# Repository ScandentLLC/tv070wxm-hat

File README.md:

# TV070WXM-HAT

A Raspberry Pi 5 HAT form-factor adapter that connects the **BOE TV070WXM-TV1-3GP1** MIPI-DSI LCD touch panel (the same display used in the LCD Steam Deck) to a Raspberry Pi 5.

<table>
  <tr>
    <td align="center"></td>
    <td align="center"></td>
  </tr>
  <tr>
    <td align="center"><b>Front</b></td>
    <td align="center"><b>Back</b></td>
  </tr>
</table>

## Description

The TV070WXM-HAT breaks out a MIPI-DSI + touch interface so you can drive the **BOE TV070WXM-TV1-3GP1** panel (the original Steam Deck LCD) directly from a Raspberry Pi 5. Two flat-flex cables carry DSI/touch between the Pi's DISP connector, the HAT, and the panel, and a 3D-printed bracket holds the whole stack together behind the display.

## What's in this repo

- **KiCad project** — schematic (with full BOM), board layout, and Gerbers, ready to send to a fab.
- **3D-printable bracket** — a simple STEP that sandwiches the Pi 5, HAT, and panel into one rigid assembly.
- **Linux Kernel patch** — a patch containing the driver and DTS files needed to make the display work on Linux.

## Parts needed for assembly

> [!WARNING]
> **This HAT is only expected to work with the official Raspberry Pi 5 27 W (5.1 V / 5 A) USB-C power supply.**
> Other power supplies will cause instability and brownouts unless they support 5 A current via USB-PD negotiation This is incredibly rare.

| Qty | Item | Digi-Key P/N | Notes |
|:---:|------|--------------|-------|
| 1 | BOE TV070WXM-TV1-3GP1 panel | — | The Steam Deck LCD panel |
| 1 | Raspberry Pi 5 (with SD card) | — | |
| 1 | Raspberry Pi 5 official 27 W PSU | — | **Required** — see warning above |
| 1 | TV070WXM-HAT | — | This project — fab it from the included Gerbers |
| 1 | FFC, Pi 5 ↔ HAT | `2073-05-22-D-0030-A-4-06-4-T-ND` | 22-pin, 0.5 mm, 30 mm, opposite-side contacts (GCT type D) |
| 1 | FFC, HAT ↔ display panel | `WM9283-ND` | Molex 0150150239 — 39-pin, 0.3 mm, 2" |
| 1 | 3D-printed bracket | — | STEP in this repo |
| 4 | 8mm M2.5X0.45 flat head screws | McMaster P/N 92010A018 | Source : McMaster Carr| 
| 4 | 2.54 mm round nylon spacers | `492-1768-ND` | Between bracket and Pi 5 |
| 4 | 11 mm M2.5×0.45 F/F standoffs | `R25-1001102-ND` | Between Pi 5 and HAT **(See note about accommodating heatsink/cooler)**|
| 4 | 8 mm M2.5×0.45 M/F standoffs | `AE10794-ND` | Above the HAT — the feet the assembly stands on |

## Assembly

> [!NOTE]
> This HAT is also compatible with the CM4 IO board, but it would require a much longer FFC between the DISP1 of the CM4 IO board and the J2 of the HAT to work. However, the hardware documentation focuses exclusively on the Raspberry Pi 5. The software documentation below includes instructions for the CM4.

### Step 1 — Mount the Pi 5 to the bracket

Using the screws, the white plastic spacers, and the female-to-female standoffs, secure the Raspberry Pi 5 to the bracket. The stack order at each corner is: **screw → spacer → Pi 5 → standoff**.
<table>
  <tr>
    <td align="center"></td>
    <td align="center"></td>
  </tr>
  </table>

### Step 2 — Connect and mount the HAT

> [!NOTE]
> To fit a Raspberry Pi 5 heatsink/active cooler between the Pi 5 and the HAT, you'll need a **taller GPIO header extender** and **longer standoffs** to clear the cooler's height. For the GPIO extender, consider Digikey P/N 1568-16763-ND, and for the longer standoffs (alternative to the 11mm standoffs), consider 25mm (Digikey P/N AE10862-ND) or 30mm (Digikey P/N 732-10626-ND)

Plug the small FFC ZIF cable into the **CAM/DISP1 connector** on the Pi 5, and plug the other end into the HAT. Seat the ZIF cable **before** mounting the HAT onto the 40-pin header — it's much easier that way. Then mount the HAT onto the Pi 5 and screw the male-female standoffs into the corners of the HAT. These are the legs the assembly stands on.
<table>
  <tr>
    <td align="center"></td>
    <td align="center"></td>
  </tr>
  </table>

### Step 3 — Connect the panel

Place the bracket on top of the display, then plug in the second FFC ZIF connector between the HAT and the display panel. Turn the assembly around and the hardware is ready.

## Driver / software

The display will not light up on hardware alone — it needs a Linux kernel panel driver and matching device-tree overlays.

This repository includes the interim kernel patch:

**[`linux-rpi-6.12.y-panel-boe-tv070wxm.patch`](./linux-rpi-6.12.y-panel-boe-tv070wxm.patch)**

The long-term plan is to submit the driver to Linux mainline. Until that happens, apply the patch against the raspberrypi/linux tree's `rpi-6.12.y` branch.

### Building the kernel

The patch was developed against the `rpi-6.12.y` branch (commit `5f23da14d91d4ba66604ec75453564e4e2afc57e`) and applies cleanly to the tip of that branch as of commit `f5a99b95354d38db209003a7d00560e5091ba94a`.

1. Obtain the Raspberry Pi kernel sources for the `rpi-6.12.y` branch.
2. Apply the patch:

   ```bash
   git apply linux-rpi-6.12.y-panel-boe-tv070wxm.patch
   ```

   (or `patch -p1 < linux-rpi-6.12.y-panel-boe-tv070wxm.patch`)

3. Enable the driver in your kernel `.config`:

   ```
   CONFIG_DRM_PANEL_BOE_TV070WXM=m
   ```

4. Build and install the kernel the same way you normally build a custom Raspberry Pi kernel. See the official [Raspberry Pi documentation](https://www.raspberrypi.com/documentation/computers/linux_kernel.html) if necessary.

Once the driver is accepted upstream you can simply use a Raspberry Pi or mainline kernel that already contains it.

> [!TIP]
> If using a custom kernel before the driver is accepted upstream, use an alternative kernel name such as `kernel_2712-custom.img` and edit config.txt to specify `kernel=kernel_2712-custom.img`. Without this, system updates will replace the kernel, causing black screens on reboot from the lack of a driver. Also, you will likely want to regenerate a corresponding initramfs using update-initramfs.

### Device-tree overlays (`config.txt`)

> [!NOTE]
> Unlike official HAT/HAT+ accessories, this does not include an ID EEPROM for auto-loaded overlays.

#### Raspberry Pi 5 (and CM5)

Add the following lines to `/boot/firmware/config.txt`:

```
display_auto_detect=0
dtoverlay=vc4-kms-v3d-pi5
dtoverlay=boe-tv070wxm-pi5
```

The Raspberry Pi 5 instructions are expected to work on the CM5 as well, but it is untested.

#### Compute Module 4

Add the following lines to `/boot/firmware/config.txt`:

```
display_auto_detect=0
dtoverlay=vc4-kms-v3d
dtoverlay=boe-tv070wxm
```

### X11 configuration (rotation & touch)

> [!NOTE]
> Only X11 is tested. Current Raspberry Pi OS defaults to Wayland. Switch to X11 in raspi-config (Advanced Options → Wayland) before using the config below.

On the Steam Deck, screen rotation is handled by `drm_panel_orientation_quirks.c` using DMI data that does not exist on the Raspberry Pi, and touch-input rotation is performed in userspace. Consequently an X11 configuration file is required (unless you prefer the display's native portrait orientation). The Linux kernel obtains a landscape orientation from the DTS for the kernel console, but nothing else uses that.

#### Raspberry Pi 5 (and CM5)

Install the following file:

```bash
cat << 'END' | sudo tee /usr/share/X11/xorg.conf.d/95-touch-rotate.conf
Section "Monitor"
    Identifier "DSI-2"
    Option "Rotate" "left"
EndSection

Section "InputClass"
    Identifier "Steam Deck Touchscreen"
    MatchProduct "hid-over-i2c 2808:1015"
    MatchIsTouchscreen "on"
    Option "TransformationMatrix" "0 -1 1 1 0 0 0 0 1"
EndSection
END
```

This is expected to work on the CM5 as well, but it is untested.

After a reboot the panel should display text in a landscape orientation with a working touchscreen.

#### Compute Module 4

Install the following file:

```bash
cat << 'END' | sudo tee /usr/share/X11/xorg.conf.d/95-touch-rotate.conf
Section "Monitor"
    Identifier "DSI-1"
    Option "Rotate" "left"
EndSection

Section "InputClass"
    Identifier "Steam Deck Touchscreen"
    MatchProduct "hid-over-i2c 2808:1015"
    MatchIsTouchscreen "on"
    Option "TransformationMatrix" "0 -1 1 1 0 0 0 0 1"
EndSection
END
```

After a reboot the panel should display text in a landscape orientation with a working touchscreen.

## Purpose

We originally developed this for our own internal use at Scandent LLC. The first iteration was an adapter board for the CM4 IO that we created as a development artifact that allowed us to bring up the Steam Deck LCD on the CM4 without investing into a full custom CM4 carrier board spin before we knew whether it would work.

We love open source and wish to share what we can with others for their reuse. Thus, after we confirmed that this worked, we redesigned our adapter board into a HAT form factor. It is our hope that others will find what we have done useful and incorporate it into their own projects. This includes the creation of commercial versions. For that reason, we have selected the CC0-1.0 license for our hardware, to ensure that there are no barriers to third party use.

For those who do incorporate this into their own CM4/CM5 carrier boards, note that very careful attention must be given to the MIPI DSI lane lengths and signal integrity.

## License

Unless otherwise specified, files in this repository are licensed under the CC0-1.0 license. See [`LICENSE`](LICENSE).

The linux kernel patch is the primary (and at the time of writing, the only) exception. It is licensed under the GPLv2.

## Credits
- Hardware engineering / documentation — Akshay Athalye
- Software engineering / documentation — Richard Yao
- HAT Evaluation / Comments — Jeff Geerling

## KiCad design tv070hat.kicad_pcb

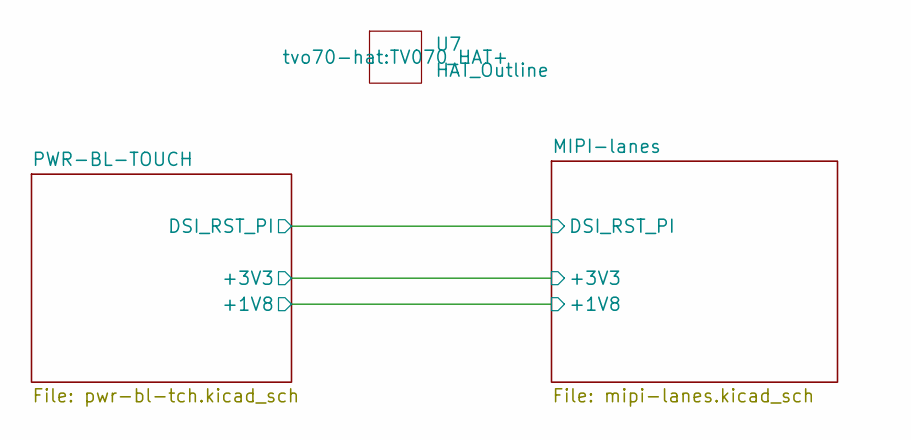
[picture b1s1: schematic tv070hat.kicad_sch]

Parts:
U7: HAT_Outline; TV070_HAT+

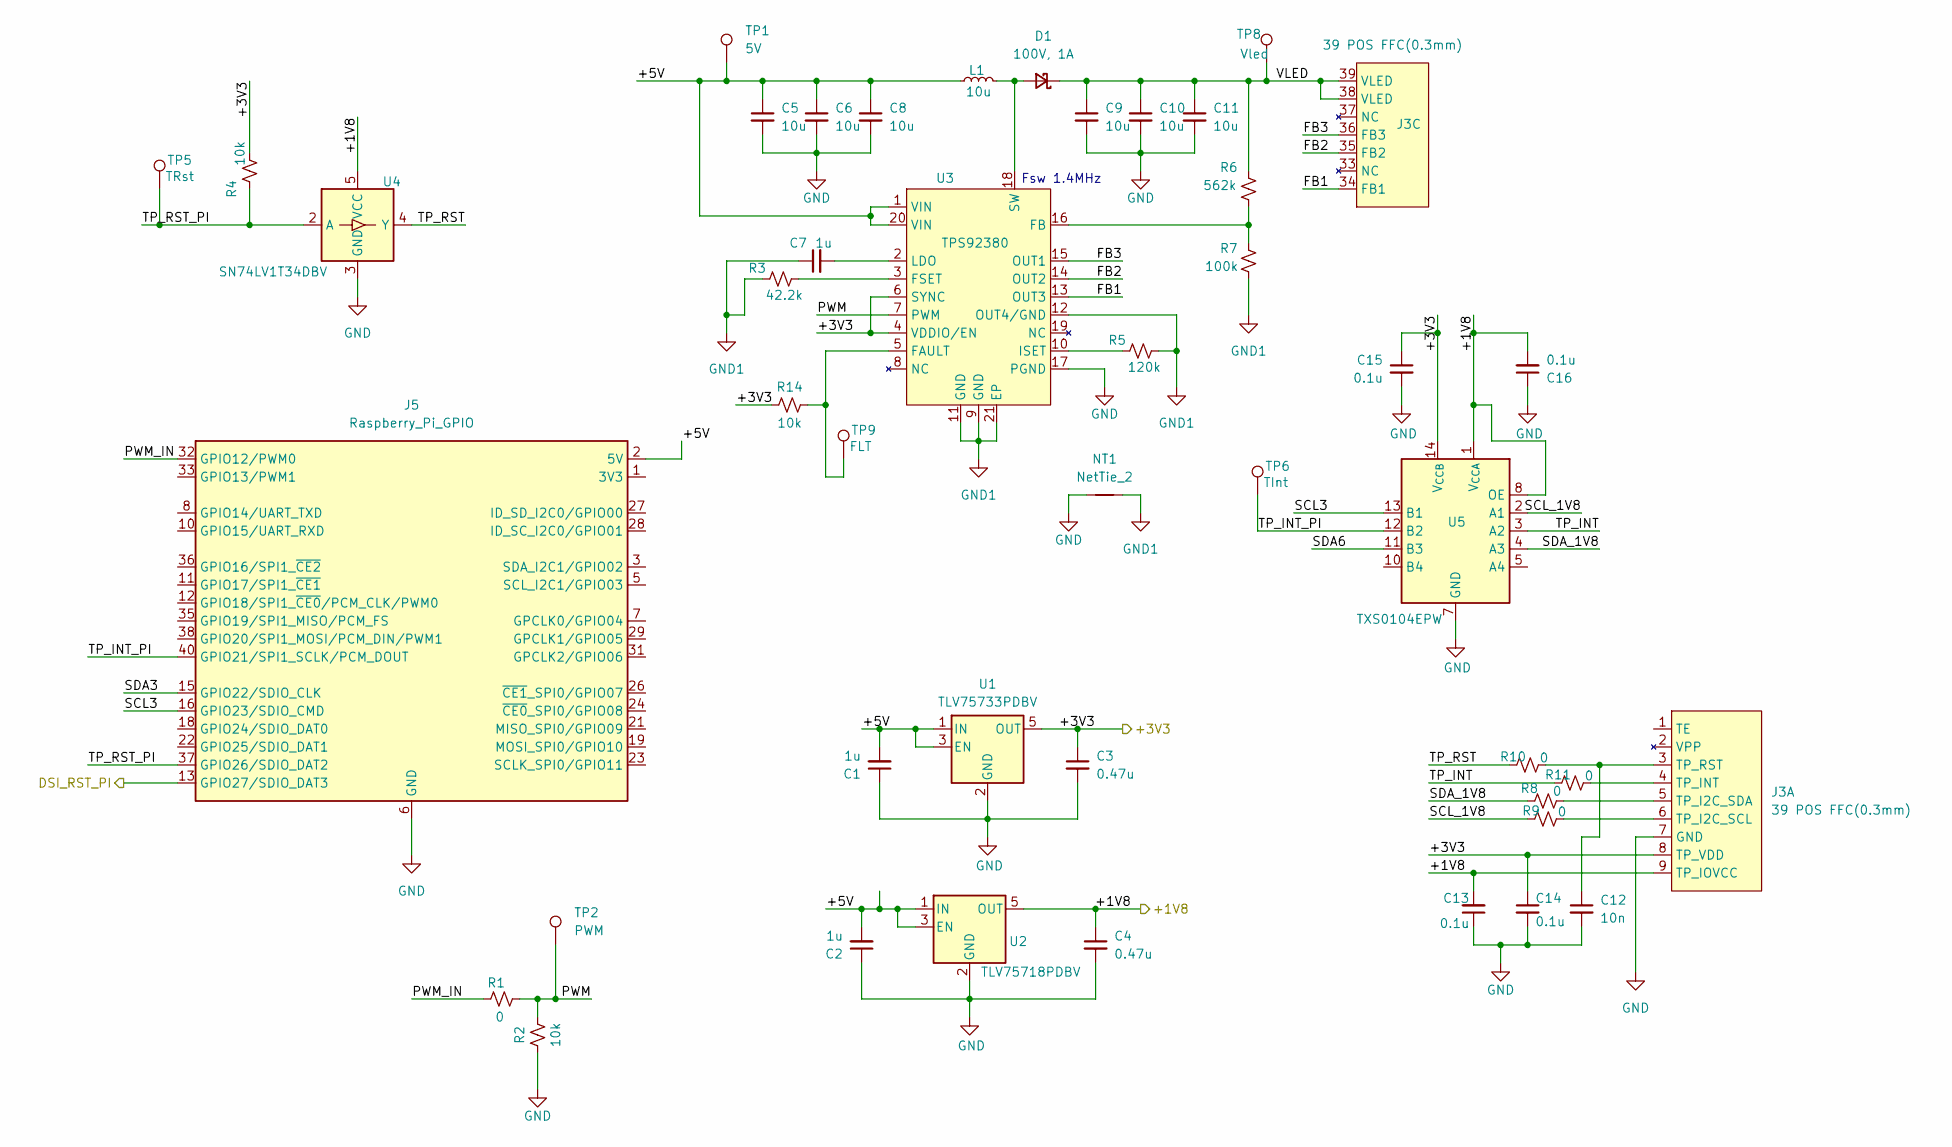
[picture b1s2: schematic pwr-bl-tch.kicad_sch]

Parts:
C1, C2, C7: 1u; C_0603_1608Metric; Mfg. Part No. CL10B105KA8NNNC; Digikey Part No. 1276-1184-1-ND
C3, C4: 0.47u; C_0603_1608Metric; Mfg. Part No. CL10B474KA8NFNC; Digikey Part No. 1276-2082-1-ND
C5, C6, C8: 10u; C_0805_2012Metric; Mfg. Part No. CL21B106KAYQNNE; Digikey Part No. 1276-CL21B106KAYQNNECT-ND
C9, C10, C11: 10u; C_1206_3216Metric; Mfg. Part No. CL31B106KBHNNNE; Digikey Part No. 1276-6767-1-ND
C12: 10n; C_0402_1005Metric; Mfg. Part No. GRM155R71C103KA01D; Digikey Part No. 490-1313-1-ND
C13, C14: 0.1u; C_0402_1005Metric; Mfg. Part No. CL05B104KP5NNNC; Digikey Part No. 1276-1002-1-ND
C15, C16: 0.1u; C_0603_1608Metric; Mfg. Part No. CL10B104KO8NNNC; Digikey Part No. 1276-1005-1-ND
D1: 100V, 1A; D_SMA; Mfg. Part No. VS-10MQ100HM3/5AT; Digikey Part No. VS-10MQ100HM3/5ATGICT-ND
J3: 39 POS FFC(0.3mm); Hirose-FH26W-39S-0.3SHW(60)-Flipped; Mfg. Part No. FH26W-39S-0.3SHW(60); Digikey Part No. H125803CT-ND
J5: Raspberry_Pi_GPIO; PinSocket_2x20_P2.54mm_Vertical; Mfg. Part No. 2222; Digikey Part No. 1528-2222-ND
L1: 10u; L_BMRF00060630; Mfg. Part No. BMRF00060630100MA1; Digikey Part No. 553-BMRF00060630100MA1CT-ND
NT1: NetTie_2; NetTie-2_SMD_Pad2.0mm
R1: 0; R_0603_1608Metric; Mfg. Part No. CRG0603ZR; Digikey Part No. A106051CT-ND
R2, R4, R14: 10k; R_0603_1608Metric; Mfg. Part No. CRG0603F10K; Digikey Part No. A106048CT-ND
R3: 42.2k; R_0603_1608Metric; Mfg. Part No. ERA-3AEB4222V; Digikey Part No. P42.2KDBCT-ND
R5: 120k; R_0603_1608Metric; Mfg. Part No. ERA-3AEB124V; Digikey Part No. P120KDBCT-ND
R6: 562k; R_0603_1608Metric; Mfg. Part No. RT0603DRE07562KL; Digikey Part No. 311-2621-1-ND
R7: 100k; R_0603_1608Metric; Mfg. Part No. RC0603FR-07100KL; Digikey Part No. 311-100KHRCT-ND
R8, R9, R10, R11: 0; R_0402_1005Metric; Digikey Part No. 311-0.0JRCT-ND
TP1: 5V; TestPoint_Pad_1.0x1.0mm
TP2: PWM; TestPoint_Pad_1.0x1.0mm
TP5: TRst; TestPoint_Pad_1.0x1.0mm
TP6: TInt; TestPoint_Pad_1.0x1.0mm
TP8: Vled; TestPoint_Pad_1.0x1.0mm
TP9: FLT; TestPoint_Pad_1.0x1.0mm
U1: TLV75733PDBV; SOT-23-5; Mfg. Part No. TLV75733PDBVR; Digikey Part No. 296-50414-1-ND
U2: TLV75718PDBV; SOT-23-5; Mfg. Part No. TLV75718PDBVR; Digikey Part No. 296-50413-1-ND
U3: TPS92380; PWP0020A-IPC_C; Mfg. Part No. TPS92380PWPR; Digikey Part No. 296-TPS92380PWPRCT-ND
U4: SN74LV1T34DBV; SOT-23-5; Mfg. Part No. SN74LV1T34DBVRG4; Digikey Part No. 296-SN74LV1T34DBVRG4CT-ND
U5: TXS0104EPW; TSSOP-14_4.4x5mm_P0.65mm; Mfg. Part No. TXS0104EPWR; Digikey Part No. 296-20697-1-ND

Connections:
/MIPI-lanes/+1V8: C4.1, C13.2, C16.2, J3.9 (TP_IOVCC), U2.5 (OUT), U4.5 (VCC), U5.1 (V_{CCA}), U5.8 (OE); also elsewhere on the board
/MIPI-lanes/+3V3: C3.1, C14.1, C15.1, J3.8 (TP_VDD), R4.2, R14.1, U1.5 (OUT), U3.4 (VDDIO/EN), U3.6 (SYNC), U5.14 (V_{CCB}); also elsewhere on the board
/MIPI-lanes/DSI_RST_PI: J5.13 (GPIO27/SDIO_DAT3); also elsewhere on the board
/PWR-BL-TOUCH/+5V: C1.2, C2.2, C5.1, C6.1, C8.1, J5.2 (5V), J5.4 (5V), L1.1, TP1.1, U1.1 (IN), U1.3 (EN), U2.1 (IN), U2.3 (EN), U3.1 (VIN), U3.20 (VIN)
/PWR-BL-TOUCH/FB1: J3.34 (FB1), U3.13 (OUT3)
/PWR-BL-TOUCH/FB2: J3.35 (FB2), U3.14 (OUT2)
/PWR-BL-TOUCH/FB3: J3.36 (FB3), U3.15 (OUT1)
/PWR-BL-TOUCH/PWM: R1.2, R2.2, TP2.1, U3.7 (PWM)
/PWR-BL-TOUCH/PWM_IN: J5.32 (GPIO12/PWM0), R1.1
/PWR-BL-TOUCH/SCL3: J5.16 (GPIO23/SDIO_CMD), U5.13 (B1)
/PWR-BL-TOUCH/SCL_1V8: R9.1, U5.2 (A1)
/PWR-BL-TOUCH/SDA_1V8: R8.1, U5.4 (A3)
/PWR-BL-TOUCH/TP_INT: R11.1, U5.3 (A2)
/PWR-BL-TOUCH/TP_INT_PI: J5.40 (GPIO21/SPI1_SCLK/PCM_DOUT), TP6.1, U5.12 (B2)
/PWR-BL-TOUCH/TP_RST: R10.1, U4.4 (Y)
/PWR-BL-TOUCH/TP_RST_PI: J5.37 (GPIO26/SDIO_DAT2), R4.1, TP5.1, U4.2 (A)
/PWR-BL-TOUCH/VLED: C9.1, C10.1, C11.1, D1.1 (K), J3.38 (VLED), J3.39 (VLED), R6.2, TP8.1
GND: C1.1, C2.1, C3.2, C4.2, C5.2, C6.2, C8.2, C9.2, C10.2, C11.2, C12.2, C13.1, C14.2, C15.2, C16.1, J3.7 (GND), J5.6 (GND), J5.9 (GND), J5.14 (GND), J5.20 (GND), J5.25 (GND), J5.30 (GND), J5.34 (GND), J5.39 (GND), NT1.1, R2.1, U1.2 (GND), U2.2 (GND), U3.17 (PGND), U4.3 (GND), U5.7 (GND); also elsewhere on the board
GND1: C7.1, NT1.2, R3.1, R5.2, R7.1, U3.9 (GND), U3.11 (GND), U3.12 (OUT4/GND), U3.21 (EP)
unnamed: D1.2 (A), L1.2, U3.18 (SW)
unnamed: J3.6 (TP_I2C_SCL), R9.2
unnamed: J3.5 (TP_I2C_SDA), R8.2
unnamed: J3.4 (TP_INT), R11.2
unnamed: C12.1, J3.3 (TP_RST), R10.2
unnamed: J5.1 (3V3), J5.17 (3V3)
unnamed: R14.2, TP9.1, U3.5 (FAULT)
unnamed: R6.1, R7.2, U3.16 (FB)
unnamed: R3.2, U3.3 (FSET)
unnamed: R5.1, U3.10 (ISET)
unnamed: C7.2, U3.2 (LDO)

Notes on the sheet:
Fsw 1.4MHz

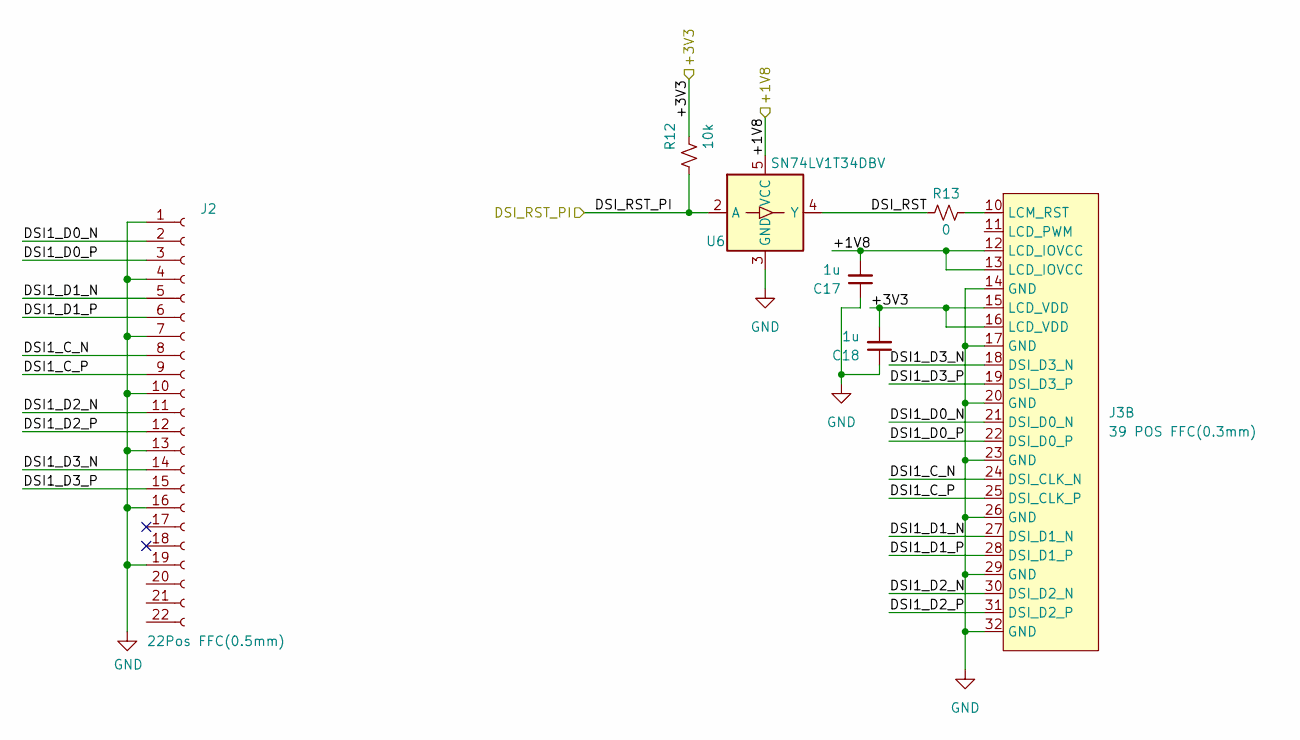
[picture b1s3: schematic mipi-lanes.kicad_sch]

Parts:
C17, C18: 1u; C_0402_1005Metric; Mfg. Part No. CL05B105KQ5NQNC; Digikey Part No. 1276-1513-1-ND
J2: 22Pos FFC(0.5mm); Hirose_FH12-22S-0.5SH_1x22-1MP_P0.50mm_Horizontal; Part Description 22 Position FFC, FPC Connector Contacts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; Digikey Part No. HFJ122CT-ND
J3: 39 POS FFC(0.3mm); Hirose-FH26W-39S-0.3SHW(60)-Flipped; Mfg. Part No. FH26W-39S-0.3SHW(60); Digikey Part No. H125803CT-ND
R12: 10k; R_0603_1608Metric; Mfg. Part No. CRG0603F10K; Digikey Part No. A106048CT-ND
R13: 0; R_0402_1005Metric; Digikey Part No. 311-0.0JRCT-ND
U6: SN74LV1T34DBV; SOT-23-5; Mfg. Part No. SN74LV1T34DBVRG4; Digikey Part No. 296-SN74LV1T34DBVRG4CT-ND

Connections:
/MIPI-lanes/+1V8: C17.2, J3.12 (LCD_IOVCC), J3.13 (LCD_IOVCC), U6.5 (VCC); also elsewhere on the board
/MIPI-lanes/+3V3: C18.2, J3.15 (LCD_VDD), J3.16 (LCD_VDD), R12.2; also elsewhere on the board
/MIPI-lanes/DSI1_C_N: J2.8, J3.24 (DSI_CLK_N)
/MIPI-lanes/DSI1_C_P: J2.9, J3.25 (DSI_CLK_P)
/MIPI-lanes/DSI1_D0_N: J2.2, J3.21 (DSI_D0_N)
/MIPI-lanes/DSI1_D0_P: J2.3, J3.22 (DSI_D0_P)
/MIPI-lanes/DSI1_D1_N: J2.5, J3.27 (DSI_D1_N)
/MIPI-lanes/DSI1_D1_P: J2.6, J3.28 (DSI_D1_P)
/MIPI-lanes/DSI1_D2_N: J2.11, J3.30 (DSI_D2_N)
/MIPI-lanes/DSI1_D2_P: J2.12, J3.31 (DSI_D2_P)
/MIPI-lanes/DSI1_D3_N: J2.14, J3.18 (DSI_D3_N)
/MIPI-lanes/DSI1_D3_P: J2.15, J3.19 (DSI_D3_P)
/MIPI-lanes/DSI_RST: R13.1, U6.4 (Y)
/MIPI-lanes/DSI_RST_PI: R12.1, U6.2 (A); also elsewhere on the board
GND: C17.1, C18.1, J2.1, J2.4, J2.7, J2.10, J2.13, J2.16, J2.19, J3.14 (GND), J3.17 (GND), J3.20 (GND), J3.23 (GND), J3.26 (GND), J3.29 (GND), J3.32 (GND), U6.3 (GND); also elsewhere on the board
unnamed: J3.10 (LCM_RST), R13.2

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
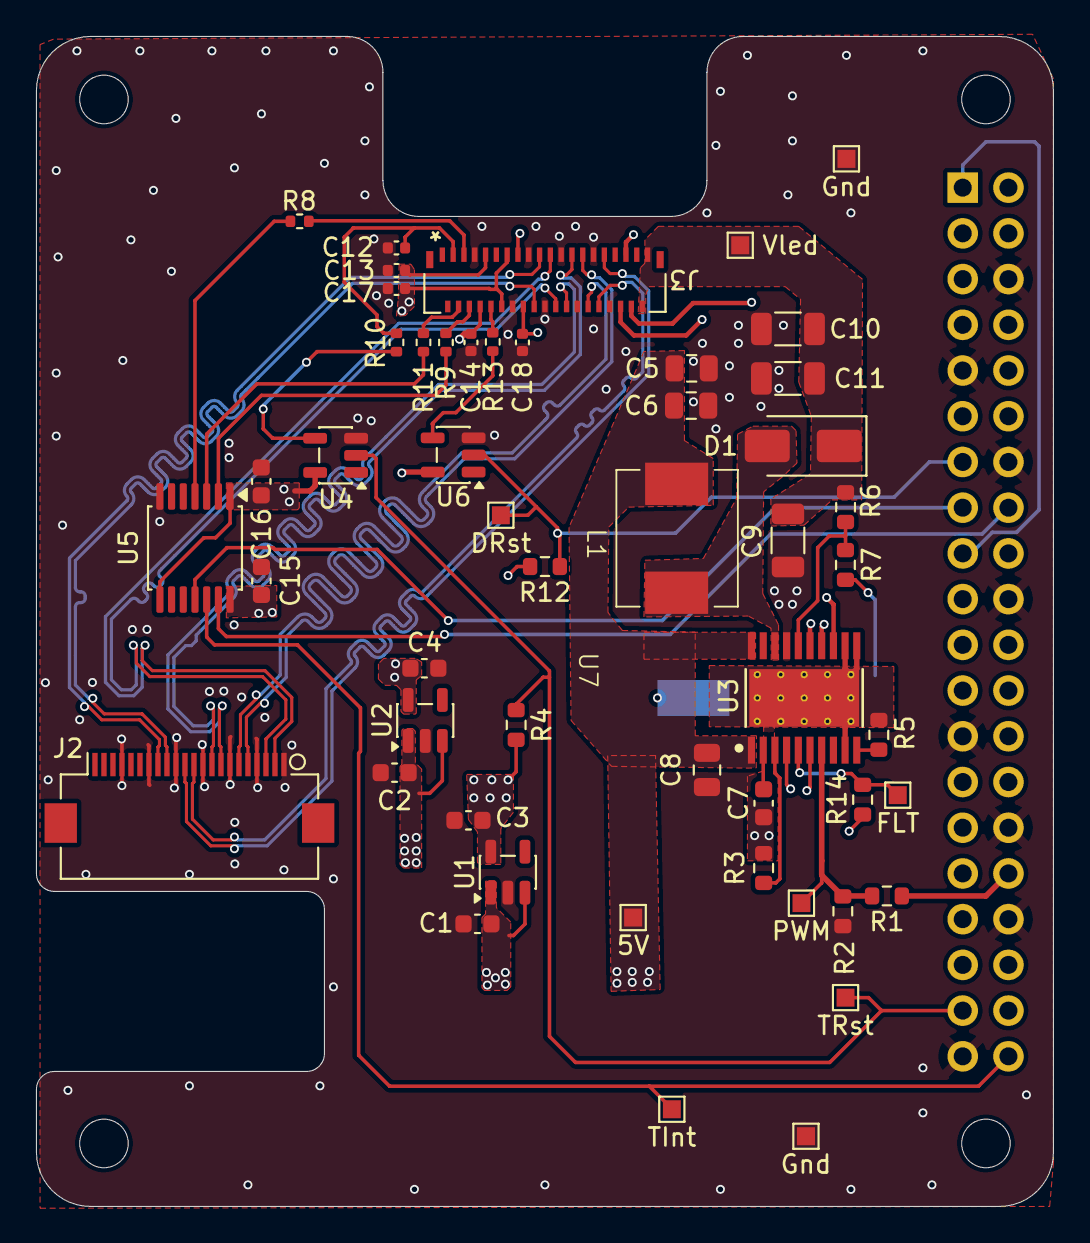
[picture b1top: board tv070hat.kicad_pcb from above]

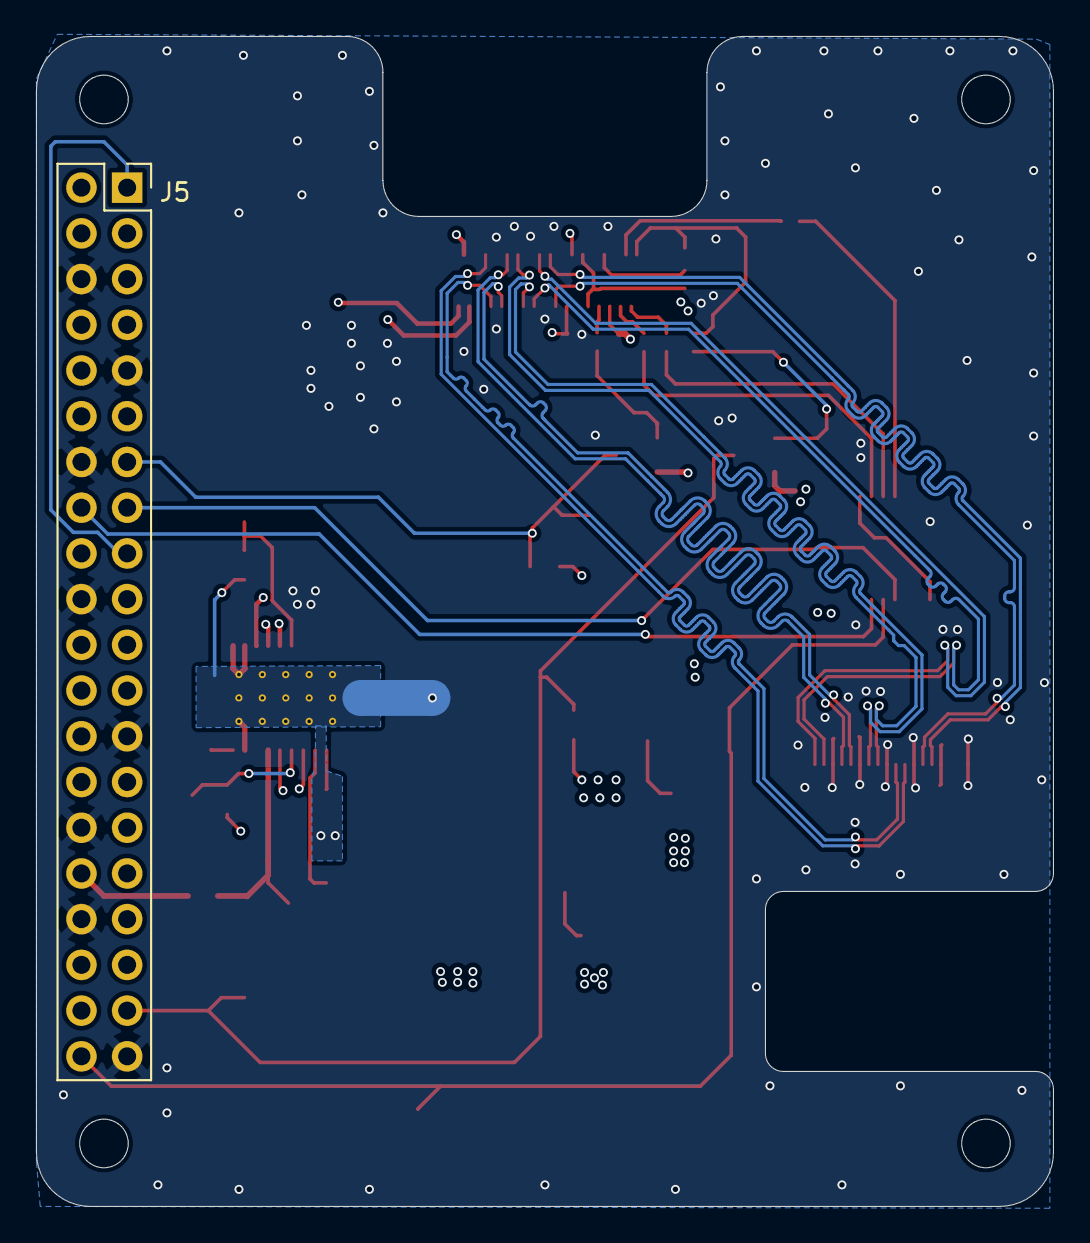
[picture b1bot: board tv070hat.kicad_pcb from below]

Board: 4 copper layers, 56.5 x 65.0 mm, 54 parts (2 on the bottom side), 43 nets.

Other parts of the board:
TP3, TP4: Gnd; TestPoint_Pad_1.0x1.0mm
TP7: DRst; TestPoint_Pad_1.0x1.0mm

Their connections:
/MIPI-lanes/DSI_RST_PI: TP7.1; also elsewhere on the board
GND: TP3.1, TP4.1; also elsewhere on the board
